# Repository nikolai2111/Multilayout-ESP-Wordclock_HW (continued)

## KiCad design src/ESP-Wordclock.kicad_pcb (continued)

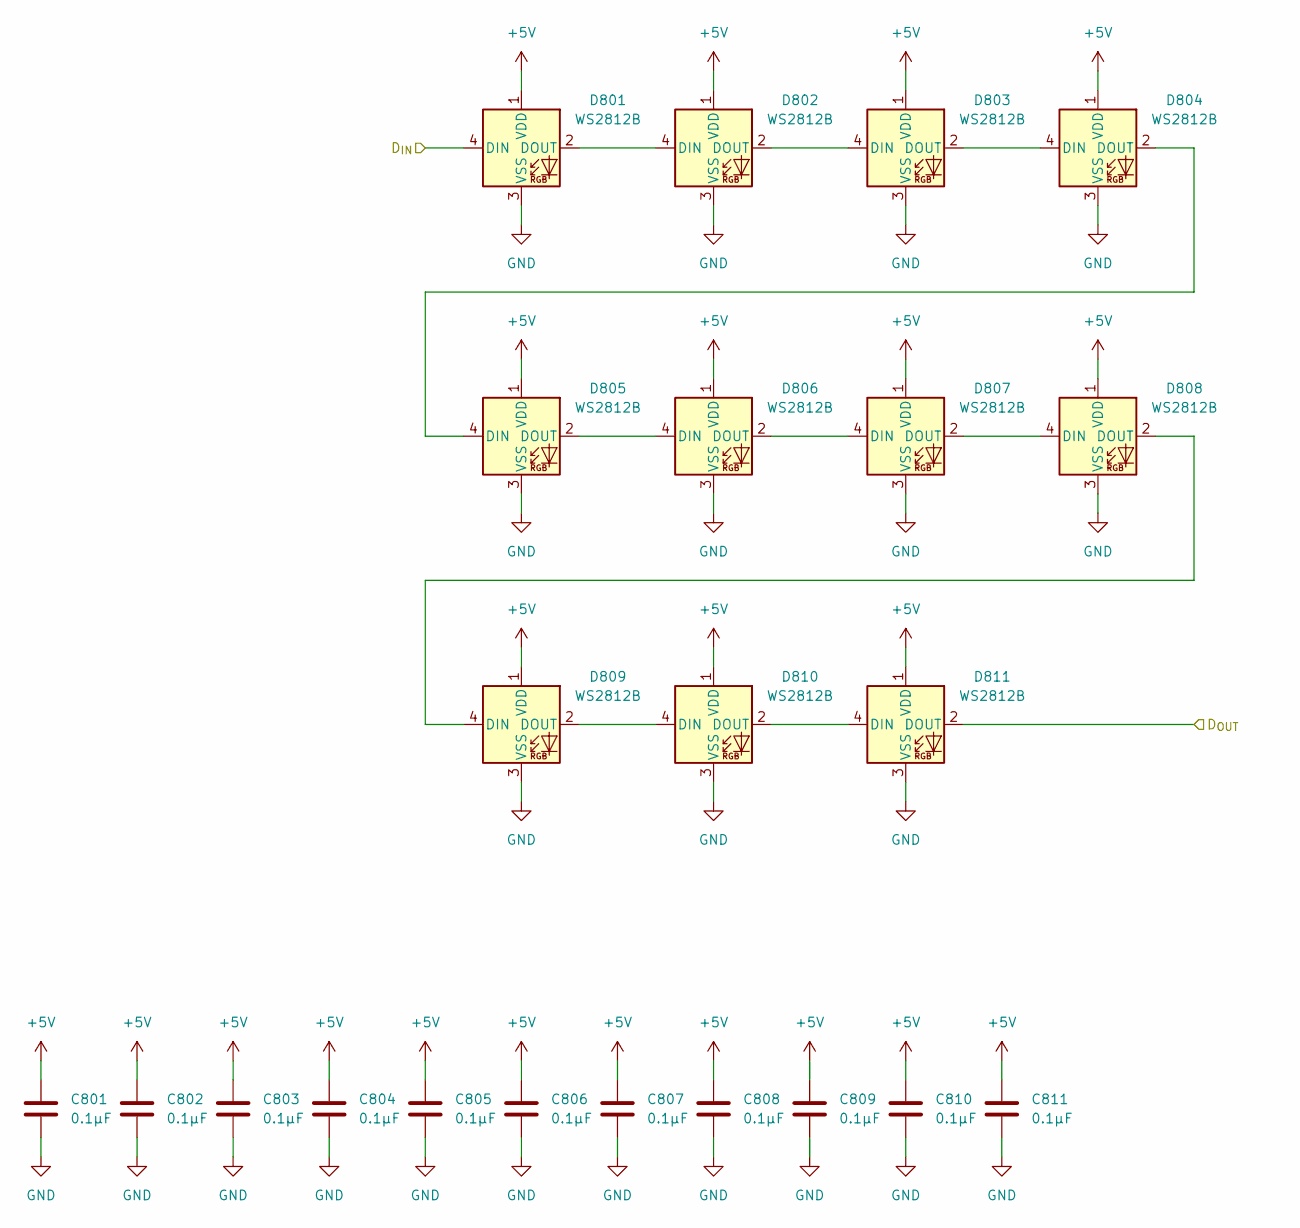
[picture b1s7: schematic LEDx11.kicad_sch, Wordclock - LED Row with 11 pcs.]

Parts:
C801, C802, C803, C804, C805, C806, C807, C808, C809, C810, C811: 0.1µF; C_0805_2012Metric_Pad1.18x1.45mm_HandSolder; Manufacturer Part no. CL21B104KCFNNNE
D801, D802, D803, D804, D805, D806, D807, D808, D809, D810, D811: WS2812B; LED_WS2812B_PLCC4_5.0x5.0mm_P3.2mm; Manufacturer Part no. WS2812B; LCSC C22461793

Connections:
+5V: C801.1, C802.1, C803.1, C804.1, C805.1, C806.1, C807.1, C808.1, C809.1, C810.1, C811.1, D801.1 (VDD), D802.1 (VDD), D803.1 (VDD), D804.1 (VDD), D805.1 (VDD), D806.1 (VDD), D807.1 (VDD), D808.1 (VDD), D809.1 (VDD), D810.1 (VDD), D811.1 (VDD); also elsewhere on the board
/LEDs/LED11-1/D_{IN}: D801.4 (DIN); also elsewhere on the board
/LEDs/LED11-1/D_{OUT}: D811.2 (DOUT); also elsewhere on the board
GND: C801.2, C802.2, C803.2, C804.2, C805.2, C806.2, C807.2, C808.2, C809.2, C810.2, C811.2, D801.3 (VSS), D802.3 (VSS), D803.3 (VSS), D804.3 (VSS), D805.3 (VSS), D806.3 (VSS), D807.3 (VSS), D808.3 (VSS), D809.3 (VSS), D810.3 (VSS), D811.3 (VSS); also elsewhere on the board
unnamed: D801.2 (DOUT), D802.4 (DIN)
unnamed: D802.2 (DOUT), D803.4 (DIN)
unnamed: D803.2 (DOUT), D804.4 (DIN)
unnamed: D804.2 (DOUT), D805.4 (DIN)
unnamed: D805.2 (DOUT), D806.4 (DIN)
unnamed: D806.2 (DOUT), D807.4 (DIN)
unnamed: D807.2 (DOUT), D808.4 (DIN)
unnamed: D808.2 (DOUT), D809.4 (DIN)
unnamed: D809.2 (DOUT), D810.4 (DIN)
unnamed: D810.2 (DOUT), D811.4 (DIN)

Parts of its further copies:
C901, C902, C903, C904, C905, C906, C907, C908, C909, C910, C911, C1001, C1002, C1003, C1004, C1005, C1006, C1007, C1008, C1009, C1010, C1011, C1101, C1102, C1103, C1104, C1105, C1106, C1107, C1108, C1109, C1110, C1111, C1201, C1202, C1203, C1204, C1205, C1206, C1207, C1208, C1209, C1210, C1211, C1301, C1302, C1303, C1304, C1305, C1306, C1307, C1308, C1309, C1310, C1311, C1401, C1402, C1403, C1404, C1405, C1406, C1407, C1408, C1409, C1410, C1411, C1501, C1502, C1503, C1504, C1505, C1506, C1507, C1508, C1509, C1510, C1511, C1601, C1602, C1603, C1604, C1605, C1606, C1607, C1608, C1609, C1610, C1611, C1701, C1702, C1703, C1704, C1705, C1706, C1707, C1708, C1709, C1710, C1711: 0.1µF; C_0805_2012Metric_Pad1.18x1.45mm_HandSolder; Manufacturer Part no. CL21B104KCFNNNE
D901, D902, D903, D904, D905, D906, D907, D908, D909, D910, D911, D1001, D1002, D1003, D1004, D1005, D1006, D1007, D1008, D1009, D1010, D1011, D1101, D1102, D1103, D1104, D1105, D1106, D1107, D1108, D1109, D1110, D1111, D1201, D1202, D1203, D1204, D1205, D1206, D1207, D1208, D1209, D1210, D1211, D1301, D1302, D1303, D1304, D1305, D1306, D1307, D1308, D1309, D1310, D1311, D1401, D1402, D1403, D1404, D1405, D1406, D1407, D1408, D1409, D1410, D1411, D1501, D1502, D1503, D1504, D1505, D1506, D1507, D1508, D1509, D1510, D1511, D1601, D1602, D1603, D1604, D1605, D1606, D1607, D1608, D1609, D1610, D1611, D1701, D1702, D1703, D1704, D1705, D1706, D1707, D1708, D1709, D1710, D1711: WS2812B; LED_WS2812B_PLCC4_5.0x5.0mm_P3.2mm; Manufacturer Part no. WS2812B; LCSC C22461793

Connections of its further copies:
+5V: C901.1, C902.1, C903.1, C904.1, C905.1, C906.1, C907.1, C908.1, C909.1, C910.1, C911.1, C1001.1, C1002.1, C1003.1, C1004.1, C1005.1, C1006.1, C1007.1, C1008.1, C1009.1, C1010.1, C1011.1, C1101.1, C1102.1, C1103.1, C1104.1, C1105.1, C1106.1, C1107.1, C1108.1, C1109.1, C1110.1, C1111.1, C1201.1, C1202.1, C1203.1, C1204.1, C1205.1, C1206.1, C1207.1, C1208.1, C1209.1, C1210.1, C1211.1, C1301.1, C1302.1, C1303.1, C1304.1, C1305.1, C1306.1, C1307.1, C1308.1, C1309.1, C1310.1, C1311.1, C1401.1, C1402.1, C1403.1, C1404.1, C1405.1, C1406.1, C1407.1, C1408.1, C1409.1, C1410.1, C1411.1, C1501.1, C1502.1, C1503.1, C1504.1, C1505.1, C1506.1, C1507.1, C1508.1, C1509.1, C1510.1, C1511.1, C1601.1, C1602.1, C1603.1, C1604.1, C1605.1, C1606.1, C1607.1, C1608.1, C1609.1, C1610.1, C1611.1, C1701.1, C1702.1, C1703.1, C1704.1, C1705.1, C1706.1, C1707.1, C1708.1, C1709.1, C1710.1, C1711.1, D901.1 (VDD), D902.1 (VDD), D903.1 (VDD), D904.1 (VDD), D905.1 (VDD), D906.1 (VDD), D907.1 (VDD), D908.1 (VDD), D909.1 (VDD), D910.1 (VDD), D911.1 (VDD), D1001.1 (VDD), D1002.1 (VDD), D1003.1 (VDD), D1004.1 (VDD), D1005.1 (VDD), D1006.1 (VDD), D1007.1 (VDD), D1008.1 (VDD), D1009.1 (VDD), D1010.1 (VDD), D1011.1 (VDD), D1101.1 (VDD), D1102.1 (VDD), D1103.1 (VDD), D1104.1 (VDD), D1105.1 (VDD), D1106.1 (VDD), D1107.1 (VDD), D1108.1 (VDD), D1109.1 (VDD), D1110.1 (VDD), D1111.1 (VDD), D1201.1 (VDD), D1202.1 (VDD), D1203.1 (VDD), D1204.1 (VDD), D1205.1 (VDD), D1206.1 (VDD), D1207.1 (VDD), D1208.1 (VDD), D1209.1 (VDD), D1210.1 (VDD), D1211.1 (VDD), D1301.1 (VDD), D1302.1 (VDD), D1303.1 (VDD), D1304.1 (VDD), D1305.1 (VDD), D1306.1 (VDD), D1307.1 (VDD), D1308.1 (VDD), D1309.1 (VDD), D1310.1 (VDD), D1311.1 (VDD), D1401.1 (VDD), D1402.1 (VDD), D1403.1 (VDD), D1404.1 (VDD), D1405.1 (VDD), D1406.1 (VDD), D1407.1 (VDD), D1408.1 (VDD), D1409.1 (VDD), D1410.1 (VDD), D1411.1 (VDD), D1501.1 (VDD), D1502.1 (VDD), D1503.1 (VDD), D1504.1 (VDD), D1505.1 (VDD), D1506.1 (VDD), D1507.1 (VDD), D1508.1 (VDD), D1509.1 (VDD), D1510.1 (VDD), D1511.1 (VDD), D1601.1 (VDD), D1602.1 (VDD), D1603.1 (VDD), D1604.1 (VDD), D1605.1 (VDD), D1606.1 (VDD), D1607.1 (VDD), D1608.1 (VDD), D1609.1 (VDD), D1610.1 (VDD), D1611.1 (VDD), D1701.1 (VDD), D1702.1 (VDD), D1703.1 (VDD), D1704.1 (VDD), D1705.1 (VDD), D1706.1 (VDD), D1707.1 (VDD), D1708.1 (VDD), D1709.1 (VDD), D1710.1 (VDD), D1711.1 (VDD); also elsewhere on the board
/LEDs/LED04-1/D_{IN}: D1711.2 (DOUT); also elsewhere on the board
/LEDs/LED11-1/D_{OUT}: D901.4 (DIN); also elsewhere on the board
/LEDs/LED11-2/D_{OUT}: D911.2 (DOUT), D1001.4 (DIN)
/LEDs/LED11-3/D_{OUT}: D1011.2 (DOUT), D1101.4 (DIN)
/LEDs/LED11-4/D_{OUT}: D1111.2 (DOUT), D1201.4 (DIN)
/LEDs/LED11-5/D_{OUT}: D1211.2 (DOUT), D1301.4 (DIN)
/LEDs/LED11-6/D_{OUT}: D1311.2 (DOUT), D1401.4 (DIN)
/LEDs/LED11-7/D_{OUT}: D1411.2 (DOUT), D1501.4 (DIN)
/LEDs/LED11-8/D_{OUT}: D1511.2 (DOUT), D1601.4 (DIN)
/LEDs/LED11-10/D_{IN}: D1611.2 (DOUT), D1701.4 (DIN)
GND: C901.2, C902.2, C903.2, C904.2, C905.2, C906.2, C907.2, C908.2, C909.2, C910.2, C911.2, C1001.2, C1002.2, C1003.2, C1004.2, C1005.2, C1006.2, C1007.2, C1008.2, C1009.2, C1010.2, C1011.2, C1101.2, C1102.2, C1103.2, C1104.2, C1105.2, C1106.2, C1107.2, C1108.2, C1109.2, C1110.2, C1111.2, C1201.2, C1202.2, C1203.2, C1204.2, C1205.2, C1206.2, C1207.2, C1208.2, C1209.2, C1210.2, C1211.2, C1301.2, C1302.2, C1303.2, C1304.2, C1305.2, C1306.2, C1307.2, C1308.2, C1309.2, C1310.2, C1311.2, C1401.2, C1402.2, C1403.2, C1404.2, C1405.2, C1406.2, C1407.2, C1408.2, C1409.2, C1410.2, C1411.2, C1501.2, C1502.2, C1503.2, C1504.2, C1505.2, C1506.2, C1507.2, C1508.2, C1509.2, C1510.2, C1511.2, C1601.2, C1602.2, C1603.2, C1604.2, C1605.2, C1606.2, C1607.2, C1608.2, C1609.2, C1610.2, C1611.2, C1701.2, C1702.2, C1703.2, C1704.2, C1705.2, C1706.2, C1707.2, C1708.2, C1709.2, C1710.2, C1711.2, D901.3 (VSS), D902.3 (VSS), D903.3 (VSS), D904.3 (VSS), D905.3 (VSS), D906.3 (VSS), D907.3 (VSS), D908.3 (VSS), D909.3 (VSS), D910.3 (VSS), D911.3 (VSS), D1001.3 (VSS), D1002.3 (VSS), D1003.3 (VSS), D1004.3 (VSS), D1005.3 (VSS), D1006.3 (VSS), D1007.3 (VSS), D1008.3 (VSS), D1009.3 (VSS), D1010.3 (VSS), D1011.3 (VSS), D1101.3 (VSS), D1102.3 (VSS), D1103.3 (VSS), D1104.3 (VSS), D1105.3 (VSS), D1106.3 (VSS), D1107.3 (VSS), D1108.3 (VSS), D1109.3 (VSS), D1110.3 (VSS), D1111.3 (VSS), D1201.3 (VSS), D1202.3 (VSS), D1203.3 (VSS), D1204.3 (VSS), D1205.3 (VSS), D1206.3 (VSS), D1207.3 (VSS), D1208.3 (VSS), D1209.3 (VSS), D1210.3 (VSS), D1211.3 (VSS), D1301.3 (VSS), D1302.3 (VSS), D1303.3 (VSS), D1304.3 (VSS), D1305.3 (VSS), D1306.3 (VSS), D1307.3 (VSS), D1308.3 (VSS), D1309.3 (VSS), D1310.3 (VSS), D1311.3 (VSS), D1401.3 (VSS), D1402.3 (VSS), D1403.3 (VSS), D1404.3 (VSS), D1405.3 (VSS), D1406.3 (VSS), D1407.3 (VSS), D1408.3 (VSS), D1409.3 (VSS), D1410.3 (VSS), D1411.3 (VSS), D1501.3 (VSS), D1502.3 (VSS), D1503.3 (VSS), D1504.3 (VSS), D1505.3 (VSS), D1506.3 (VSS), D1507.3 (VSS), D1508.3 (VSS), D1509.3 (VSS), D1510.3 (VSS), D1511.3 (VSS), D1601.3 (VSS), D1602.3 (VSS), D1603.3 (VSS), D1604.3 (VSS), D1605.3 (VSS), D1606.3 (VSS), D1607.3 (VSS), D1608.3 (VSS), D1609.3 (VSS), D1610.3 (VSS), D1611.3 (VSS), D1701.3 (VSS), D1702.3 (VSS), D1703.3 (VSS), D1704.3 (VSS), D1705.3 (VSS), D1706.3 (VSS), D1707.3 (VSS), D1708.3 (VSS), D1709.3 (VSS), D1710.3 (VSS), D1711.3 (VSS); also elsewhere on the board
unnamed: D901.2 (DOUT), D902.4 (DIN)
unnamed: D902.2 (DOUT), D903.4 (DIN)
unnamed: D903.2 (DOUT), D904.4 (DIN)
unnamed: D904.2 (DOUT), D905.4 (DIN)
unnamed: D905.2 (DOUT), D906.4 (DIN)
unnamed: D906.2 (DOUT), D907.4 (DIN)
unnamed: D907.2 (DOUT), D908.4 (DIN)
unnamed: D908.2 (DOUT), D909.4 (DIN)
unnamed: D909.2 (DOUT), D910.4 (DIN)
unnamed: D910.2 (DOUT), D911.4 (DIN)
unnamed: D1001.2 (DOUT), D1002.4 (DIN)
unnamed: D1002.2 (DOUT), D1003.4 (DIN)
unnamed: D1003.2 (DOUT), D1004.4 (DIN)
unnamed: D1004.2 (DOUT), D1005.4 (DIN)
unnamed: D1005.2 (DOUT), D1006.4 (DIN)
unnamed: D1006.2 (DOUT), D1007.4 (DIN)
unnamed: D1007.2 (DOUT), D1008.4 (DIN)
unnamed: D1008.2 (DOUT), D1009.4 (DIN)
unnamed: D1009.2 (DOUT), D1010.4 (DIN)
unnamed: D1010.2 (DOUT), D1011.4 (DIN)
unnamed: D1101.2 (DOUT), D1102.4 (DIN)
unnamed: D1102.2 (DOUT), D1103.4 (DIN)
unnamed: D1103.2 (DOUT), D1104.4 (DIN)
unnamed: D1104.2 (DOUT), D1105.4 (DIN)
unnamed: D1105.2 (DOUT), D1106.4 (DIN)
unnamed: D1106.2 (DOUT), D1107.4 (DIN)
unnamed: D1107.2 (DOUT), D1108.4 (DIN)
unnamed: D1108.2 (DOUT), D1109.4 (DIN)
unnamed: D1109.2 (DOUT), D1110.4 (DIN)
unnamed: D1110.2 (DOUT), D1111.4 (DIN)
unnamed: D1201.2 (DOUT), D1202.4 (DIN)
unnamed: D1202.2 (DOUT), D1203.4 (DIN)
unnamed: D1203.2 (DOUT), D1204.4 (DIN)
unnamed: D1204.2 (DOUT), D1205.4 (DIN)
unnamed: D1205.2 (DOUT), D1206.4 (DIN)
unnamed: D1206.2 (DOUT), D1207.4 (DIN)
unnamed: D1207.2 (DOUT), D1208.4 (DIN)
unnamed: D1208.2 (DOUT), D1209.4 (DIN)
unnamed: D1209.2 (DOUT), D1210.4 (DIN)
unnamed: D1210.2 (DOUT), D1211.4 (DIN)
unnamed: D1301.2 (DOUT), D1302.4 (DIN)
unnamed: D1302.2 (DOUT), D1303.4 (DIN)
unnamed: D1303.2 (DOUT), D1304.4 (DIN)
unnamed: D1304.2 (DOUT), D1305.4 (DIN)
unnamed: D1305.2 (DOUT), D1306.4 (DIN)
unnamed: D1306.2 (DOUT), D1307.4 (DIN)
unnamed: D1307.2 (DOUT), D1308.4 (DIN)
unnamed: D1308.2 (DOUT), D1309.4 (DIN)
unnamed: D1309.2 (DOUT), D1310.4 (DIN)
unnamed: D1310.2 (DOUT), D1311.4 (DIN)
unnamed: D1401.2 (DOUT), D1402.4 (DIN)
unnamed: D1402.2 (DOUT), D1403.4 (DIN)
unnamed: D1403.2 (DOUT), D1404.4 (DIN)
unnamed: D1404.2 (DOUT), D1405.4 (DIN)
unnamed: D1405.2 (DOUT), D1406.4 (DIN)
unnamed: D1406.2 (DOUT), D1407.4 (DIN)
unnamed: D1407.2 (DOUT), D1408.4 (DIN)
unnamed: D1408.2 (DOUT), D1409.4 (DIN)
unnamed: D1409.2 (DOUT), D1410.4 (DIN)
unnamed: D1410.2 (DOUT), D1411.4 (DIN)
unnamed: D1501.2 (DOUT), D1502.4 (DIN)
unnamed: D1502.2 (DOUT), D1503.4 (DIN)
unnamed: D1503.2 (DOUT), D1504.4 (DIN)
unnamed: D1504.2 (DOUT), D1505.4 (DIN)
unnamed: D1505.2 (DOUT), D1506.4 (DIN)
unnamed: D1506.2 (DOUT), D1507.4 (DIN)
unnamed: D1507.2 (DOUT), D1508.4 (DIN)
unnamed: D1508.2 (DOUT), D1509.4 (DIN)
unnamed: D1509.2 (DOUT), D1510.4 (DIN)
unnamed: D1510.2 (DOUT), D1511.4 (DIN)
unnamed: D1601.2 (DOUT), D1602.4 (DIN)
unnamed: D1602.2 (DOUT), D1603.4 (DIN)
unnamed: D1603.2 (DOUT), D1604.4 (DIN)
unnamed: D1604.2 (DOUT), D1605.4 (DIN)
unnamed: D1605.2 (DOUT), D1606.4 (DIN)
unnamed: D1606.2 (DOUT), D1607.4 (DIN)
unnamed: D1607.2 (DOUT), D1608.4 (DIN)
unnamed: D1608.2 (DOUT), D1609.4 (DIN)
unnamed: D1609.2 (DOUT), D1610.4 (DIN)
unnamed: D1610.2 (DOUT), D1611.4 (DIN)
unnamed: D1701.2 (DOUT), D1702.4 (DIN)
unnamed: D1702.2 (DOUT), D1703.4 (DIN)
unnamed: D1703.2 (DOUT), D1704.4 (DIN)
unnamed: D1704.2 (DOUT), D1705.4 (DIN)
unnamed: D1705.2 (DOUT), D1706.4 (DIN)
unnamed: D1706.2 (DOUT), D1707.4 (DIN)
unnamed: D1707.2 (DOUT), D1708.4 (DIN)
unnamed: D1708.2 (DOUT), D1709.4 (DIN)
unnamed: D1709.2 (DOUT), D1710.4 (DIN)
unnamed: D1710.2 (DOUT), D1711.4 (DIN)

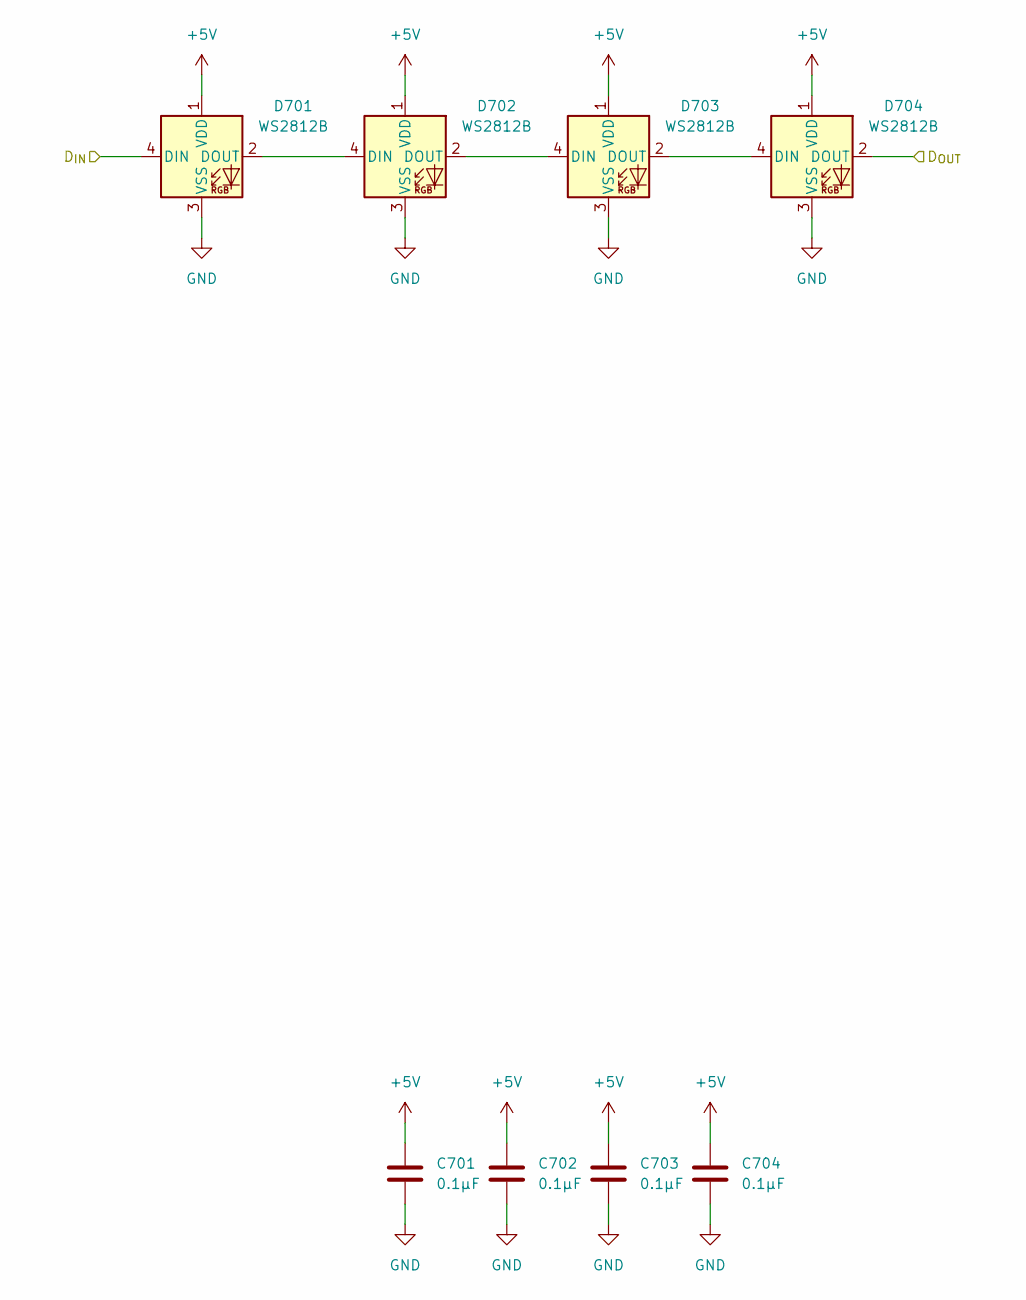
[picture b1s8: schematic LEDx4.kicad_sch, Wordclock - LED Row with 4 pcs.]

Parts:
C701, C702, C703, C704: 0.1µF; C_0805_2012Metric_Pad1.18x1.45mm_HandSolder; Manufacturer Part no. CL21B104KCFNNNE
D701, D702, D703, D704: WS2812B; LED_WS2812B_PLCC4_5.0x5.0mm_P3.2mm; Manufacturer Part no. WS2812B; LCSC C22461793

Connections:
+5V: C701.1, C702.1, C703.1, C704.1, D701.1 (VDD), D702.1 (VDD), D703.1 (VDD), D704.1 (VDD); also elsewhere on the board
/LEDs/LED04-1/D_{IN}: D701.4 (DIN); also elsewhere on the board
/LEDs/LED04-1/D_{OUT}: D704.2 (DOUT)
GND: C701.2, C702.2, C703.2, C704.2, D701.3 (VSS), D702.3 (VSS), D703.3 (VSS), D704.3 (VSS); also elsewhere on the board
unnamed: D701.2 (DOUT), D702.4 (DIN)
unnamed: D702.2 (DOUT), D703.4 (DIN)
unnamed: D703.2 (DOUT), D704.4 (DIN)

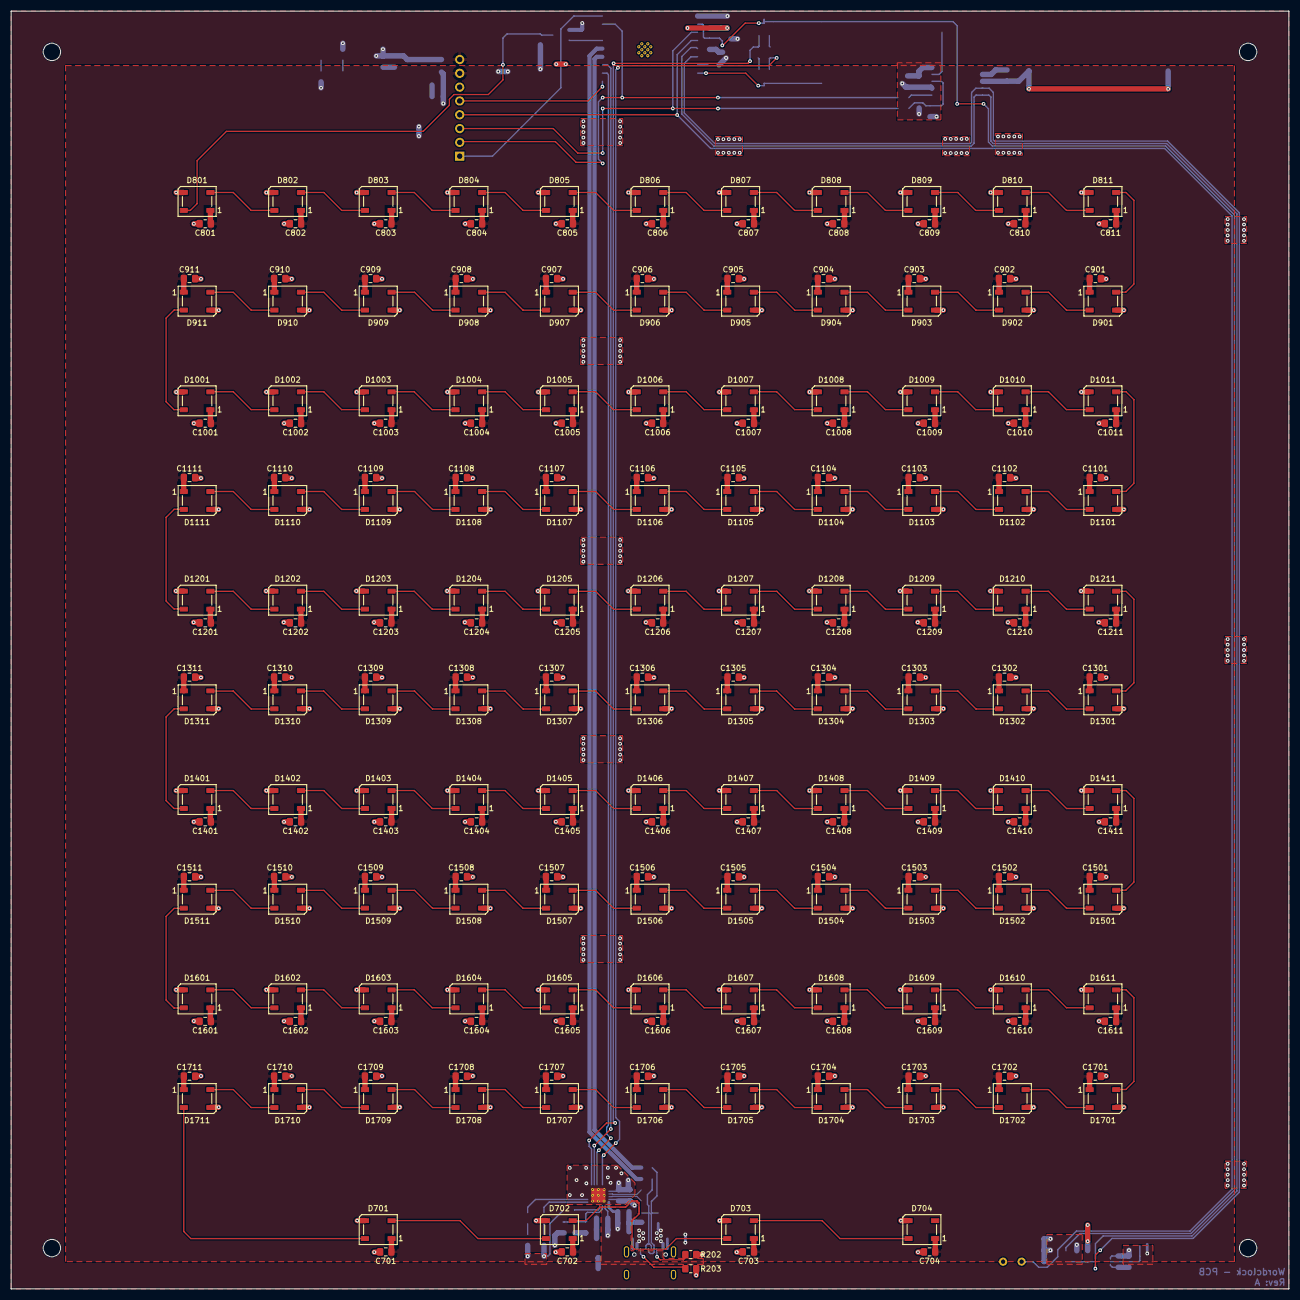
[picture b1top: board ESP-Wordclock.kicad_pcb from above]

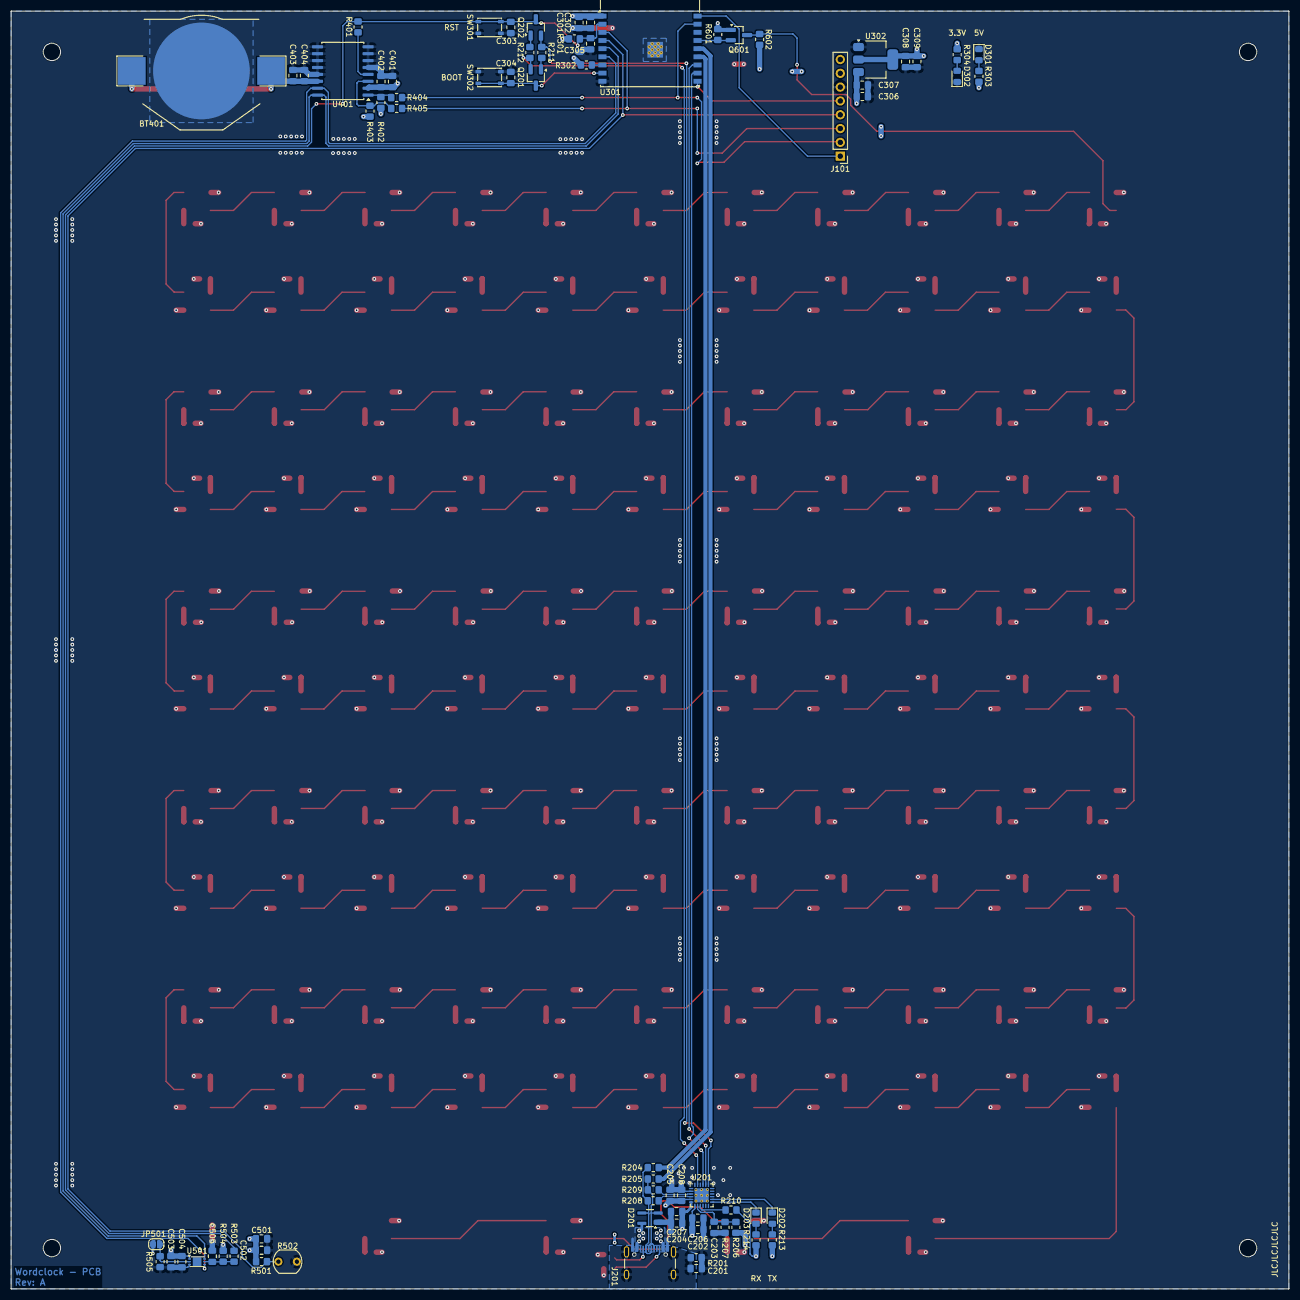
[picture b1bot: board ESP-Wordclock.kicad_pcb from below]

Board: 2 copper layers, 235.0 x 235.0 mm, 307 parts (73 on the bottom side), 157 nets.

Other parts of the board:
H1, H2, H3, H4: MountingHole_3.2mm_M3

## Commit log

2024-10-27 Add: Initial commit, changed the PCB to a submodule inside the official Multilayout-ESP-Wordclock
2024-10-27 Mod: README.md, added a small text with the link to the software
2024-10-27 Mod: .gitignore file, used my default one
2024-10-27 Del: .lck file
2024-10-27 Mod: Checked a few things and added the power limitation text to the LEDs page
2024-10-27 Mod: Changed the page number of the MCU and USB page
2024-10-27 Fix: Some errors from the ERC
2024-10-27 Add: Vendor no. and footprints
2024-10-29 Mod: Changed parts to match with both vendors
2024-10-29 Add: Schemaitc_A.pdf
2024-10-29 Add: BOM_A.pdf exported BOM as .csv and generated a .pdf form the .csv
2024-11-01 Add: Header for empty pins of the ESP32 and added more 0R resistors to break up some connections
2024-11-01 Fix: Name of the battery cell. Run ERC and created finished schematic, ready for the layout
2024-11-01 Fix: Annotation of the LEDs
2024-11-01 Add: BasePCB and added edge cut, holes, dimentions and LEDs with their caps
2024-11-01 Fix: USB labels for differential pairs
2024-11-01 Add: Componentes and created first routes
2024-11-05 Mod: Almost finished layout for the USB-C
2024-11-10 Mod: Layout, finished the layout. Changed the voltage pins of J101
2024-11-10 Add: ESP-Wordclock.step
2024-11-10 Add: Picutre and fabrication document
2024-11-10 Fix: ESP-Wordclock.kicad_pcb, run DRC and fixed errors
2024-11-12 Mod: Moved LEDs for the minutes 3 mm down and reexported all relevant files agian
2024-11-17 Add: JLCPCB Database and selected components for the assembly
2024-11-17 Add: JLCPCB order number placeholder
2024-11-17 Mod: Exported all files
2024-11-17 Fix: JLCPCB production data to be correct for production
2024-11-25 Fix: Part no. of D201, because it was the wrong one
2024-11-25 Mod: Updated date and fixed some typo
2024-11-25 Mod: Saved undsaved project file
2024-11-25 Mod: Updated the whole PCB, run DRC and re-exported all manufacturing files
2024-11-25 Fix: Wrong LCSC part no. for U401
2024-11-25 Mod: Re-exported all 3d files
